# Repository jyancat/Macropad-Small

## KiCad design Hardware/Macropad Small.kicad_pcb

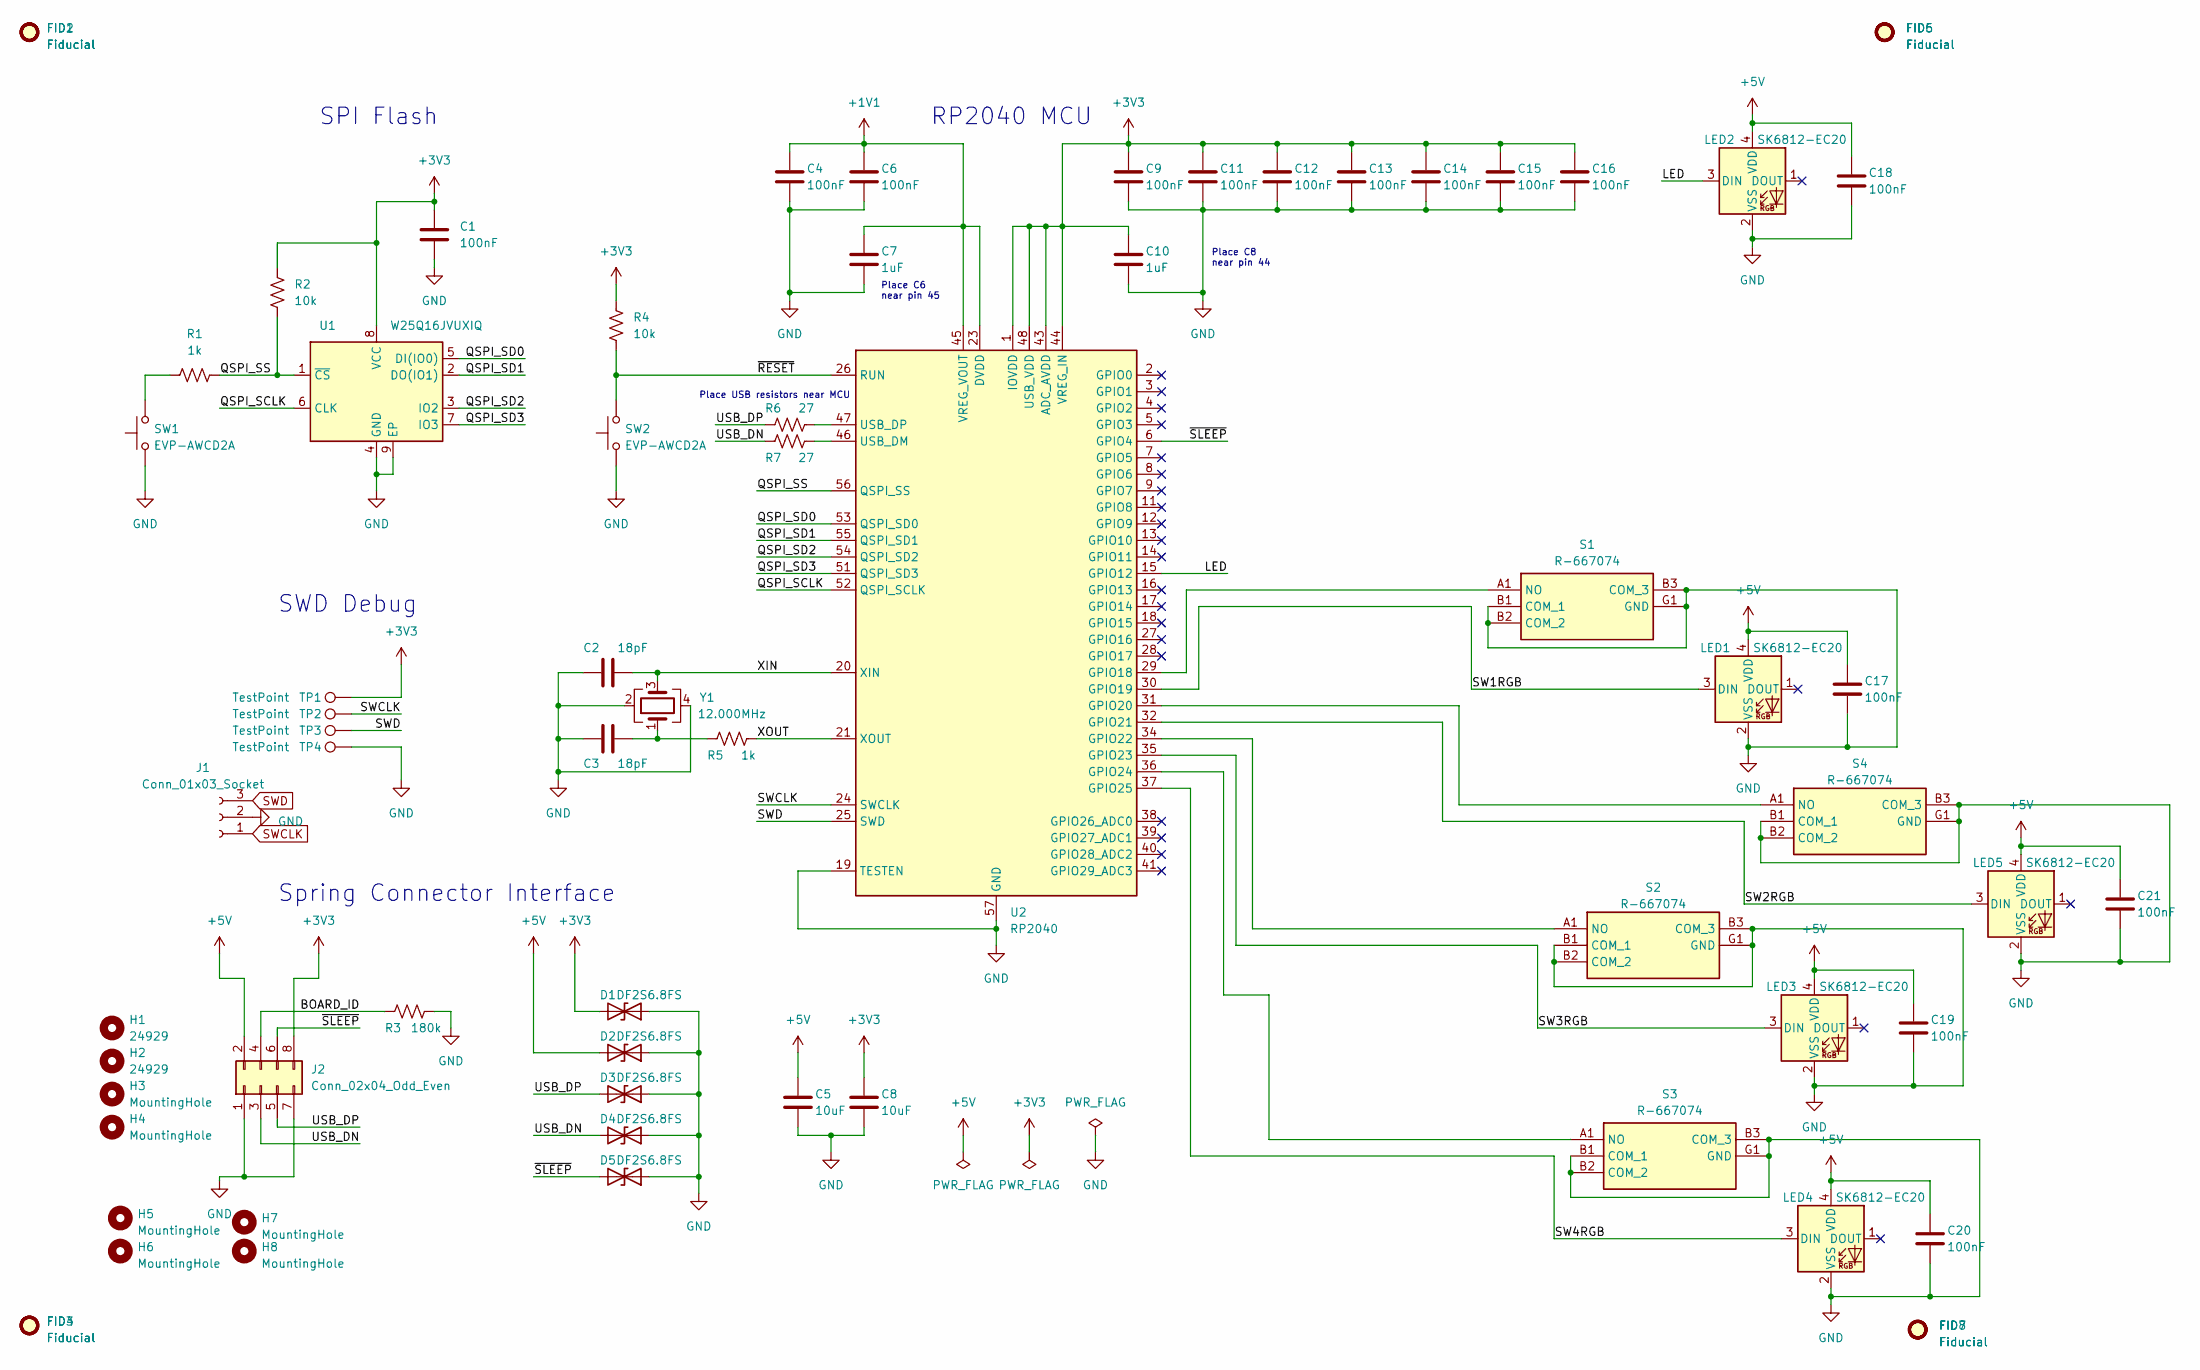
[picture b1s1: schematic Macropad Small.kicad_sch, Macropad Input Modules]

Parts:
C1, C4, C6, C9, C11, C12, C13, C14, C15, C16, C17, C18, C19, C20, C21: 100nF; C_0402_1005Metric
C2, C3: 18pF; C_0402_1005Metric
C5, C8: 10uF; C_0402_1005Metric
C7, C10: 1uF; C_0402_1005Metric
D1, D2, D3, D4, D5: DF2S6.8FS; D_SOD-923
FID1, FID2, FID3, FID4, FID5, FID6, FID7, FID8: Fiducial; Fiducial_0.75mm_Mask1.5mm
H1, H2: 24929; MountingHole_3.7mm_Pad_24929
H3, H4: MountingHole; MountingHole_2.1mm
H5, H6, H7, H8: MountingHole; MountingHole_2.2mm_M2
J1: Conn_01x03_Socket; JST_SH_BM03B-SRSS-TB_1x03-1MP_P1.00mm_Vertical
J2: Conn_02x04_Odd_Even; PogoPads_2x4_P2.0mm
LED1, LED2, LED3, LED4, LED5: SK6812-EC20
R1, R5: 1k; R_0402_1005Metric
R2, R4: 10k; R_0402_1005Metric
R3: 180k; R_0402_1005Metric
R6, R7: 27; R_0402_1005Metric
S1, S2, S3, S4: R-667074; R667074; Manufacturer_Part_Number R-667074
SW1, SW2: EVP-AWCD2A; SW_SPST_CK_KXT3
TP1, TP2, TP3, TP4: TestPoint; TestPoint_Pad_D1.0mm
U1: W25Q16JVUXIQ; SON-8-1EP_3x2mm_P0.5mm_EP0.2x1.6mm
U2: RP2040; QFN-56-1EP_7x7mm_P0.4mm_EP3.2x3.2mm
Y1: 12.000MHz; Crystal_SMD_5032-4Pin_5.0x3.2mm; MPN K12000J074

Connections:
+1V1: C4.1, C6.1, C7.1, U2.23 (DVDD), U2.45 (VREG_VOUT), U2.50 (DVDD)
+3V3: C1.1, C8.1, C9.1, C10.1, C11.1, C12.1, C13.1, C14.1, C15.1, C16.1, D1.2 (A2), J2.8, R2.1, R4.1, TP1.1, U1.8 (VCC), U2.1 (IOVDD), U2.10 (IOVDD), U2.22 (IOVDD), U2.33 (IOVDD), U2.42 (IOVDD), U2.43 (ADC_AVDD), U2.44 (VREG_IN), U2.48 (USB_VDD), U2.49 (IOVDD)
+5V: C5.1, C17.1, C18.1, C19.1, C20.1, C21.1, D2.2 (A2), J2.2, LED1.4 (VDD), LED2.4 (VDD), LED3.4 (VDD), LED4.4 (VDD), LED5.4 (VDD)
/BOARD_ID: J2.4, R3.1
/LED: LED2.3 (DIN), U2.15 (GPIO12)
/QSPI_SCLK: U1.6 (CLK), U2.52 (QSPI_SCLK)
/QSPI_SD0: U1.5 (DI(IO0)), U2.53 (QSPI_SD0)
/QSPI_SD1: U1.2 (DO(IO1)), U2.55 (QSPI_SD1)
/QSPI_SD2: U1.3 (IO2), U2.54 (QSPI_SD2)
/QSPI_SD3: U1.7 (IO3), U2.51 (QSPI_SD3)
/QSPI_SS: R1.2, R2.2, U1.1 (~CS), U2.56 (QSPI_SS)
/SW1RGB: LED1.3 (DIN), U2.30 (GPIO19)
/SW2RGB: LED5.3 (DIN), U2.32 (GPIO21)
/SW3RGB: LED3.3 (DIN), U2.35 (GPIO23)
/SW4RGB: LED4.3 (DIN), U2.37 (GPIO25)
/USB_DN: D4.2 (A2), J2.3, R7.1
/USB_DP: D3.2 (A2), J2.5, R6.1
/XIN: C2.2, U2.20 (XIN), Y1.3
/XOUT: R5.2, U2.21 (XOUT)
/~RESET: R4.2, SW2.2, U2.26 (RUN)
/~SLEEP: D5.2 (A2), J2.6, U2.6 (GPIO4)
GND: C1.2, C2.1, C3.1, C4.2, C5.2, C6.2, C7.2, C8.2, C9.2, C10.2, C11.2, C12.2, C13.2, C14.2, C15.2, C16.2, C17.2, C18.2, C19.2, C20.2, C21.2, D1.1 (A1), D2.1 (A1), D3.1 (A1), D4.1 (A1), D5.1 (A1), J1.2, J1.MP, J2.1, J2.7, LED1.2 (VSS), LED2.2 (VSS), LED3.2 (VSS), LED4.2 (VSS), LED5.2 (VSS), R3.2, S1.B1 (COM_1), S1.B2 (COM_2), S1.B3 (COM_3), S1.G1 (GND), S2.B1 (COM_1), S2.B2 (COM_2), S2.B3 (COM_3), S2.G1 (GND), S3.B1 (COM_1), S3.B2 (COM_2), S3.B3 (COM_3), S3.G1 (GND), S4.B1 (COM_1), S4.B2 (COM_2), S4.B3 (COM_3), S4.G1 (GND), SW1.1, SW2.1, TP4.1, U1.4 (GND), U1.9 (EP), U2.19 (TESTEN), U2.57 (GND), Y1.2, Y1.4
unnamed: C3.2, R5.1, Y1.1
unnamed: R1.1, SW1.2
unnamed: S1.A1 (NO), U2.29 (GPIO18)
unnamed: S2.A1 (NO), U2.34 (GPIO22)
unnamed: S3.A1 (NO), U2.36 (GPIO24)
unnamed: S4.A1 (NO), U2.31 (GPIO20)
unnamed: R7.2, U2.46 (USB_DM)
unnamed: R6.2, U2.47 (USB_DP)
SWCLK: J1.1, TP2.1, U2.24 (SWCLK)
SWD: J1.3, TP3.1, U2.25 (SWD)

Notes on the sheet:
SPI Flash
Place C8 near pin 44
Place USB resistors near MCU
Spring Connector Interface
Place C6 near pin 45
RP2040 MCU
SWD Debug

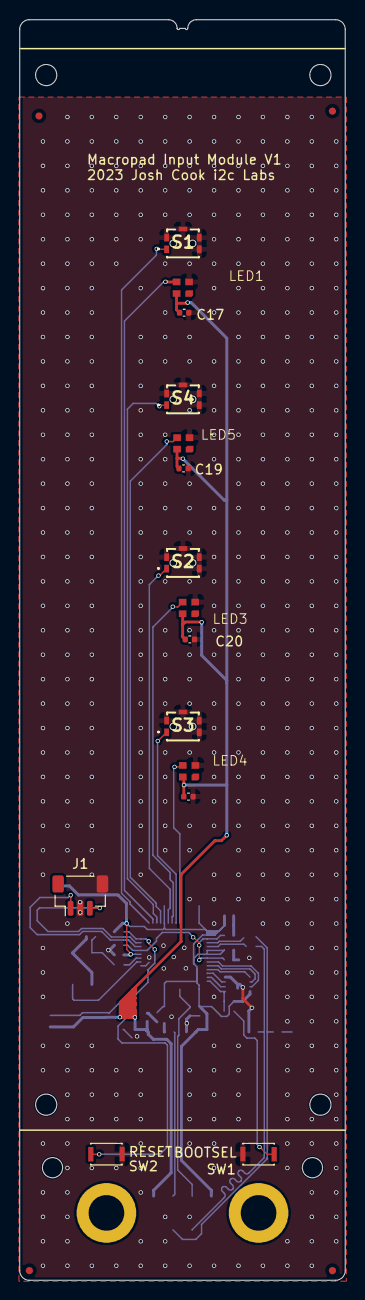
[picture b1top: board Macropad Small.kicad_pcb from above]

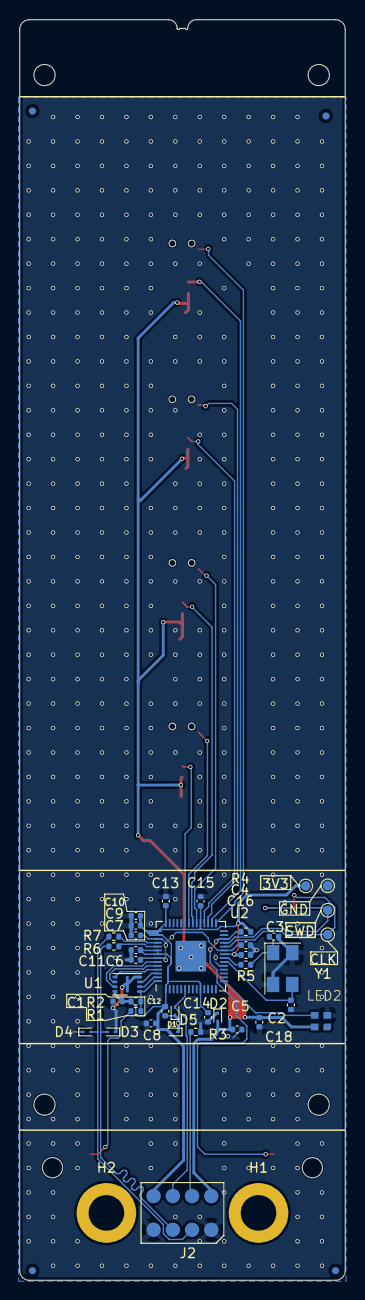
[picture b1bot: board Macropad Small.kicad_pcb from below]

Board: 2 copper layers, 33.8 x 131.0 mm, 69 parts (44 on the bottom side), 32 nets.

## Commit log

2023-07-27 Add new files

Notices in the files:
Hardware/Macropad Small.kicad_pcb:
This work is licensed under a Creative Commons Attribution 4.0 International License
